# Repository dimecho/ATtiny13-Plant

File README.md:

# ATtiny13 Plant

Monitor soil moisture and water plant. Portable and high efficiency with lithium-ion batteries.

## Download

 [MacOS](../../releases/download/1.0/ATtiny13-Plant.dmg)

 [Windows](../../releases/download/1.0/ATtiny13-Plant.zip)

 [Linux](../../releases/download/1.0/ATtiny13-Plant.tgz)

 [Firmware](../../releases/download/1.0/ATtiny13-Plant-Firmware.zip)

## BOM (Bill of Materials)

| Part  | Value      | Package             | Function |
| ----- |:----------:| -------------------:|---------:|
| IC1   | ATTINY13A  | SOP-8 or DIP-8      | CPU      |
| C1    | 100nF      | 0805 or 0603 (104)  | CPU      |
| T1A/B | 2N4401 NPN | TO-92 or SOT-23     | Pump     |
| R1    | 100R       | 0805 or 0603 (101)  | Pump     |
| R2    | 10k        | 0805 or 0603 (103)  | Pump     |
| R6    | 10k        | 0805 or 0603 (103)  | Sensor   |
| LED1  | Red        | 0805 or DIP-2       | LED      |
| R7    | 1k         | 0805 or 0603 (102)  | LED      |
| -     | 3.7-4.2V   | Lithium 18650       | Battery  |
| -     | TP4056     | Lithium Charger     | Charger  |

## PCB

Designed with [EagleCAD](https://www.autodesk.com/products/eagle/free-download)

## Diagram

## Compile

Install "avr-gcc" and run "make".

> [MacOS](https://ww1.microchip.com/downloads/en/DeviceDoc/avr8-gnu-toolchain-osx-3.6.2.503-darwin.any.x86_64.tar.gz)
>
> [Windows](https://ww1.microchip.com/downloads/en/DeviceDoc/avr8-gnu-toolchain-3.6.2.1759-win32.any.x86.zip)

```
avr-gcc -std=gnu99 -Wall -Os -mmcu=attiny13a main.c -o main.o
avr-objcopy -O binary main.o main.bin
avr-objcopy -O ihex main.o main.hex
```

## Flash

```
avrdude -p t13 -c usbtiny -Uhfuse:w:0xFB:m -Ulfuse:w:0x6A:m -U flash:w:main.hex:i
```

There are 3 options to flash ATtiny13 chip.

1. [USBtiny](usbtiny) (built-in)
2. [USBasp](usbasp)
3. [Raspberry Pi](usbpi)

## Licenses

> ATtiny13 Plant
>
> 
>
> USBasp / USBtiny
>
>

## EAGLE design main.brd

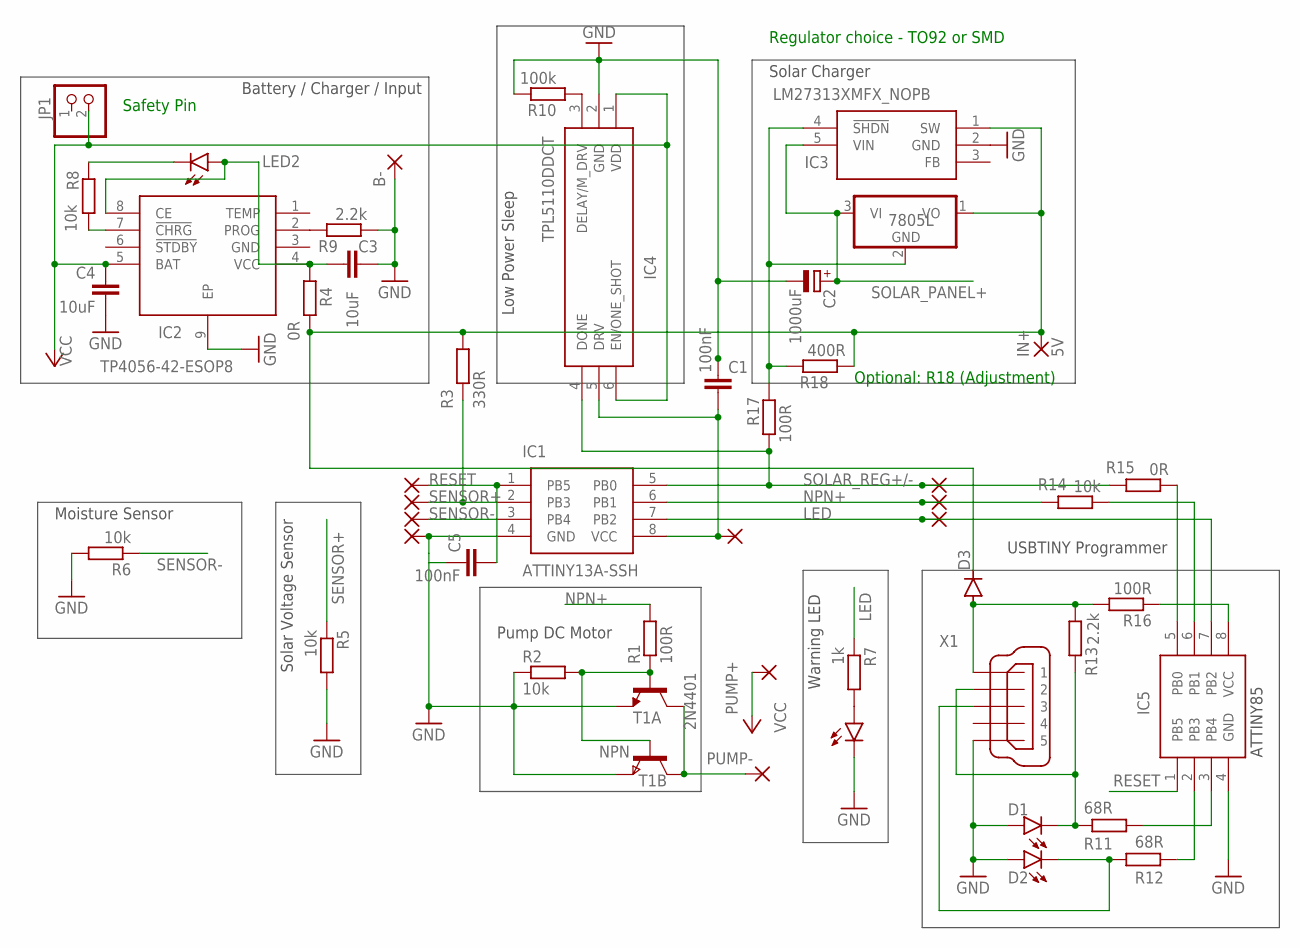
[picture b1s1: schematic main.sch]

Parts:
B-: 1,6/0,8
C1, C5: 100nF; C0805
C2: 1000uF; E2,5-7
C3: 10uF; C3216
C4: 10uF; C0805
D1, D2: LEDSML0805; SML0805
D3: DIODE-MINIMELF; MINIMELF
IC1, IC5: ATTINY13A-SSH; SOIC127P600X175-8N
IC2: TP4056-42-ESOP8; SOIC127P600X175-9N
IC3: LM27313XMFX_NOPB; SOT95P280X145-5N
IC4: TPL5110DDCT; SOT95P280X110-6N
IN+: 5V; 1,6/0,9
JP1: PINHD-1X2; 1X02
LED1, LED2: LEDSML0805; SML0805
PAD3, PAD4, PAD5, PAD6, PAD7, PAD8, PAD9, PAD10: 1,6/0,8
PUMP+: 2,15/1,0
PUMP-: 2,15/1,0
R1: 100R; R0805
R2, R5, R6: 10k; R0805
R3: 330R; R0805
R4: 0R; M1206
R7: 1k; R0805
R8: 10k; R0603
R9, R13: 2.2k; R0603
R10: 100k; R0603
R11, R12: 68R; R0603
R14: 10k; R0402
R15: 0R; R0402
R16, R17: 100R; R0603
R18: 400R; R0603
REG1: 7805L; TO92
T1A: 2N4401; TO92
T1B: NPN; SOT-23
X1: MINI-USB-UX60A-MB-5ST; UX60A-MB-5ST

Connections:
GND: B-.1, C1.1, C2.-, C3.2, C4.2, C5.1, D1.A, D2.A, IC1.4 (GND), IC2.9 (EP), IC3.2 (GND), IC4.2 (GND), IC5.4 (GND), LED1.C, PAD7.1, R2.1, R5.2, R6.2, R9.2, R10.2, T1A.1 (E), T1B.2 (E), X1.5
LED: IC1.7 (PB2), IC5.7 (PB2), PAD4.1, R7.1
unnamed: R1.1, R2.2, T1A.2 (B), T1B.3 (B)
unnamed: PUMP-.1, T1A.3 (C), T1B.1 (C)
unnamed: C1.2, IC1.8 (VCC), IC4.5 (DRV), PAD3.1
unnamed: C3.1, IC2.4 (VCC), IC2.8 (CE), LED2.A, R4.2
unnamed: D3.C, IC3.1 (SW), IN+.1, R3.2, R4.1, R18.1, REG1.1 (VO)
unnamed: LED1.A, R7.2
unnamed: IC4.3 (DELAY/M_DRV), R10.1
unnamed: IC2.7 (!CHRG), R8.2
unnamed: LED2.C, R8.1
unnamed: IC5.3 (PB4), R11.2
unnamed: IC2.2 (PROG), R9.1
unnamed: IC5.2 (PB3), R12.2
unnamed: D1.C, R11.1, R13.2, X1.2
unnamed: D2.C, R12.1, X1.3
unnamed: IC5.6 (PB1), R14.1
unnamed: IC5.5 (PB0), R15.1
unnamed: IC5.8 (VCC), R16.1
unnamed: IC3.4 (!SHDN), R17.2, R18.2, REG1.2 (GND)
unnamed: D3.A, R13.1, R16.2, X1.1
NPN+: IC1.6 (PB1), PAD6.1, R1.2, R14.2
RESET: C5.2, IC1.1 (PB5), IC5.1 (PB5), PAD10.1
SENSOR+: IC1.2 (PB3), PAD9.1, R3.1, R5.1
SENSOR-: IC1.3 (PB4), PAD8.1, R6.1
SOLAR_PANEL+: C2.+, IC3.5 (VIN), REG1.3 (VI)
SOLAR_REG+/-: IC1.5 (PB0), IC4.4 (DONE), PAD5.1, R15.2, R17.1
VCC: C4.1, IC2.5 (BAT), IC4.1 (VDD), IC4.6 (EN/ONE_SHOT), JP1.2, PUMP+.1

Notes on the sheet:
Battery / Charger / Input
Solar Charger
Pump DC Motor
Warning LED
Moisture Sensor
Solar Voltage Sensor
Low Power Sleep
ATTINY85
USBTINY Programmer
Safety Pin
Regulator choice - TO92 or SMD
Optional: R18 (Adjustment)

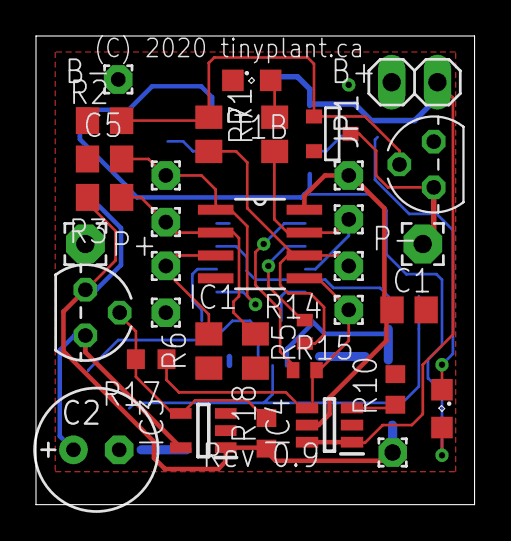
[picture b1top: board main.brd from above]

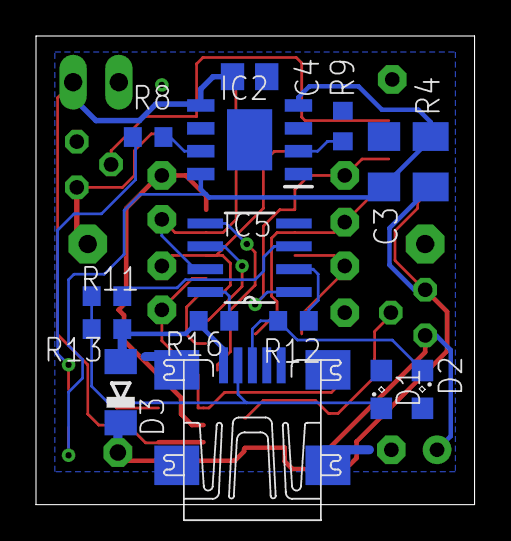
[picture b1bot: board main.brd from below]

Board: 2 copper layers, 24.4 x 26.0 mm, 50 parts (15 on the bottom side), 28 nets.

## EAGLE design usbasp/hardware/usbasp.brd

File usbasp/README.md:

USBASP KEY
==========

http://fabiobaltieri.com/2011/09/02/usb-key-avr-programmer/

This project is an AVR ISP programmer with USB interface in a compact usb
key PCB. The project is based on the original USBasp version of Thomas Fischl,
which can be found on:

http://www.fischl.de/usbasp/

Contents
--------

    COPYING     text version of the GPL
    README      this file
    binaries/   pre-built firmware images in hex format
    firmware/   source directory for firmware files
    hardware/   source directory for the hardware design files

Firmware
--------

Building requires an avr-gcc toolchain, in the firmware/ directory, to build
run:

    make main.hex

Flashing the firmware on the device requires avrdude and a compatible hardware
programmer. Default configuration is stored at the beginning of the Makefile.
To program with the default configuration, run:

    make flash

Fuses can be configured running:

    make fuses

Hardware
--------

All hardware files (schematic, layout and libraries) are in CadSoft Eagle
format.

```
avrdude -p t13 -c usbasp -Uhfuse:w:0xFB:m -Ulfuse:w:0x6A:m -U flash:w:main.hex:i
```

License
-------

This program is free software: you can redistribute it and/or modify
it under the terms of the GNU General Public License as published by
the Free Software Foundation, either version 2 of the License, or
(at your option) any later version.

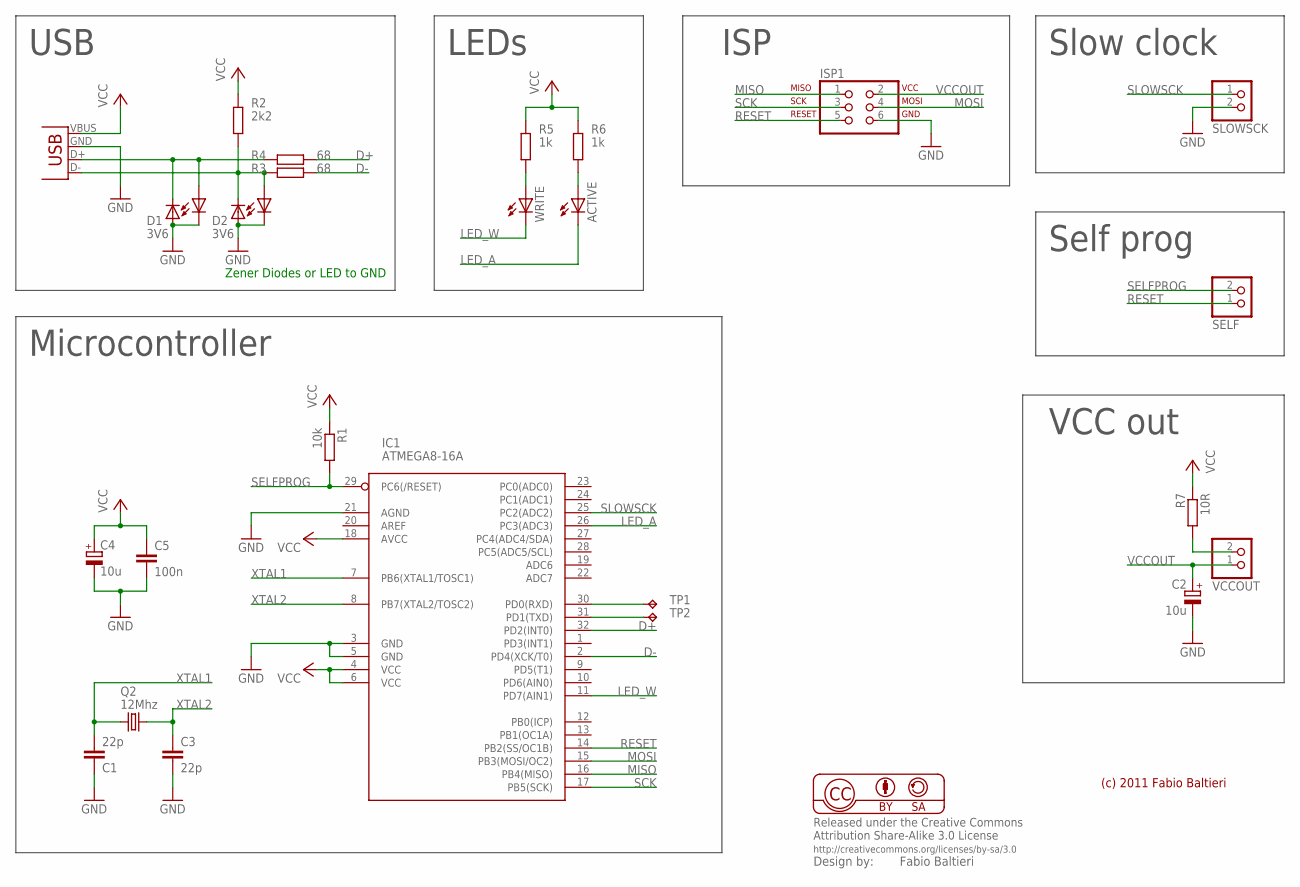
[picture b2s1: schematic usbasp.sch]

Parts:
ACTIVE: LEDCHIP-LED0805; CHIP-LED0805
C1, C3: 22p; C0805
C2, C4: 10u; SMC_A
C5: 100n; C0805
D1, D2: 3V6; SMA-DIODE
IC1: ATMEGA8-16A; TQFP32-08
ISP1: ISP-AVR910SMD; 2X03_BORDER
LED1, LED2: LEDCHIP-LED0805; CHIP-LED0805
Q2: 12Mhz; HC49US
R1: 10k; M0805
R2: 2k2; M0805
R3, R4: 68; M0805
R5, R6: 1k; M0805
R7: 10R; M0805
SELF: PINHD-1X2; 1X02
SLOWSCK: PINHD-1X2; 1X02
TP1, TP2: TPB1,27; B1,27
VCCOUT: PINHD-1X2; 1X02
WRITE: LEDCHIP-LED0805; CHIP-LED0805
X1: USB-A-H

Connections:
D+: IC1.32 (PD2(INT0)), R4.1
D-: IC1.2 (PD4(XCK/T0)), R3.1
GND: C1.1, C2.-, C3.1, C4.-, C5.2, D1.A, D2.A, IC1.3 (GND), IC1.5 (GND), IC1.21 (AGND), ISP1.6, LED1.C, LED2.C, SLOWSCK.2, X1.GND (VBUS)
LED_A: ACTIVE.C, IC1.26 (PC3(ADC3))
LED_W: IC1.11 (PD7(AIN1)), WRITE.C
MISO: IC1.16 (PB4(MISO)), ISP1.1
MOSI: IC1.15 (PB3(MOSI/OC2)), ISP1.4
unnamed: R5.2, WRITE.A
unnamed: D1.C, LED1.A, R4.2, X1.D+ (D-)
unnamed: D2.C, LED2.A, R2.1, R3.2, X1.D- (D+)
unnamed: ACTIVE.A, R6.2
unnamed: IC1.30 (PD0(RXD)), TP1.TP
unnamed: R7.2, VCCOUT.2
unnamed: IC1.31 (PD1(TXD)), TP2.TP
RESET: IC1.14 (PB2(SS/OC1B)), ISP1.5, SELF.1
SCK: IC1.17 (PB5(SCK)), ISP1.3
SELFPROG: IC1.29 (PC6(/RESET)), R1.2, SELF.2
SLOWSCK: IC1.25 (PC2(ADC2)), SLOWSCK.1
VCC: C4.+, C5.1, IC1.4 (VCC), IC1.6 (VCC), IC1.18 (AVCC), R1.1, R2.2, R5.1, R6.1, R7.1, X1.VBUS (GND)
VCCOUT: C2.+, ISP1.2, VCCOUT.1
XTAL1: C1.2, IC1.7 (PB6(XTAL1/TOSC1)), Q2.2
XTAL2: C3.2, IC1.8 (PB7(XTAL2/TOSC2)), Q2.1

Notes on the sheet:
(c) 2011 Fabio Baltieri
Microcontroller
USB
LEDs
ISP
Slow clock
Self prog
VCC out
Zener Diodes or LED to GND

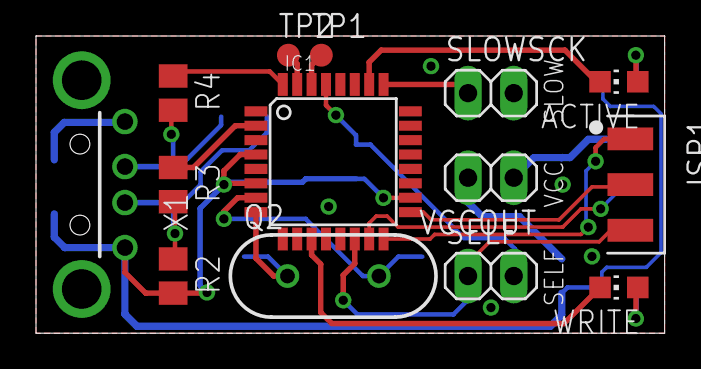
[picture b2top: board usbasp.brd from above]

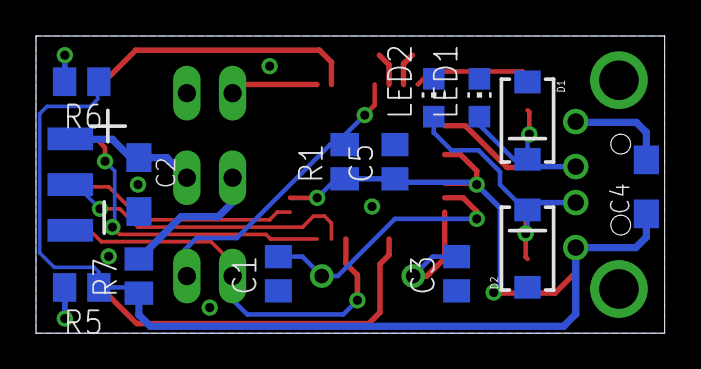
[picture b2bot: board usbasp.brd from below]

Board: 2 copper layers, 34.9 x 16.5 mm, 27 parts (13 on the bottom side), 22 nets.

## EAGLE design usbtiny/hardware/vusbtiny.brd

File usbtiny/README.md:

http://www.simpleavr.com/avr/vusbtiny

Description
-------

From http://www.xs4all.nl/~dicks/avr/usbtiny/

USBtiny is a software implementation of the USB low-speed protocol for the Atmel ATtiny microcontrollers. Of course, it will also work on the ATmega series. The software is written for an AVR clocked at 12 MHz. At this frequency, each bit on the USB bus takes 8 clock cycles, and with a lot of trickery, it is possible to decode and encode the USB waveforms by software. The USB driver needs approximately 1250 to 1350 bytes of flash space (excluding the optional identification strings), depending on the configuration and compiler version, and 46 bytes RAM (excluding stack space). The C interface consists of 3 to 5 functions, depending on the configuration.

vUSB
-------

From http://www.obdev.at/products/vusb/

V-USB is a software-only implementation of a low-speed USB device for Atmel's AVR microcontrollers, making it possible to build USB hardware with almost any AVR microcontroller, not requiring any additional chip.

Features
-------

* Programming logic from usbtiny isp, mature avr-dude support
* Small foot-print
* Minimal components
* Powers target device

Note that the IO lines to the target MCUS are not protected. you can add 1k-2k resistors to SCK and MOSI and protect against possible wrong connections

References
-------

based on the works found at

v-usb from framework http://www.obdev.at/vusb/
usbtiny isp http://www.xs4all.nl/~dicks/avr/usbtiny/

Parts List
-------

* 1x attiny45/85
* 1x 100nf capacitor (104)
* 2x 3.6v zener diodes (1n747,BZX79)
* 2x 68ohm resistor
* 1x 1.5k (1.7k) resistor

* (optional) 1k/2k resistors for io lines protection

Tools Required
-------
* A working AVR programmer (yes, it's a catch22, we need one to make one)
* Working AVR programming environment

Application Notes
-------

* vusbtiny works with avrdude and is viewed by avrdude as a usbtiny programmer
* vusbtiny always power target chip via USB
* Jumper J2 connects programmer to target chip
* When connected and NOT in programming
* Target chip w/ target RESET line high
* Other target pins (MISO, MOSI, CLK) in hi-Z state
* During programming
* Turns target RESET line LOW
* MISO becomes input
* MOSI, CLK becomes output

Schematic
-------

Building and Flashing
-------

* change into /firmware working directory
```
make
```
* attach your favorite ISP programmer
* modify makefile and change your avrdude parameters if needed. the stock one assumes USBTiny programmer. i.e. AVRDUDE_PROGRAMMERID=usbtiny
```
make install
```
After flashing firmware, we need to properly set the fuse, we are using pin 1 reset as IO in this project

* PLL clock used as required by v-usb layer for usb timing (16.5Mhz)
* reset pin disabled as we need to use it as IO
```
avrdude -c usbtiny -p t85 -V -U lfuse:w:0xe1:m -U hfuse:w:0x5d:m -U efuse:w:0xff:m
```

This setting disables further programming via 5V SPI as we need the RESET pin (pin1) for IO. you will need access to a HVSP programmer to recover the fuse.

Troubleshooting
-------

* Cannot flash the firmware? check your original programmer, might need to adjust timing via -B flag in avrdude. try to read chip 1st, may be a bad fuse, may be your chip need an external clock signal. you may need to fix your chip back to default 1st.
    check connections
* If use different io pins, check code and connections
* You may substitute zener diodes with 500mw, 400mw types
* You may try reduce R3 value to 1.2K or less
* You are more likely to encounter avrdude timing problems, try -B flag of avrdude, have a shorter USB cable all helps

License
-------

GPL2

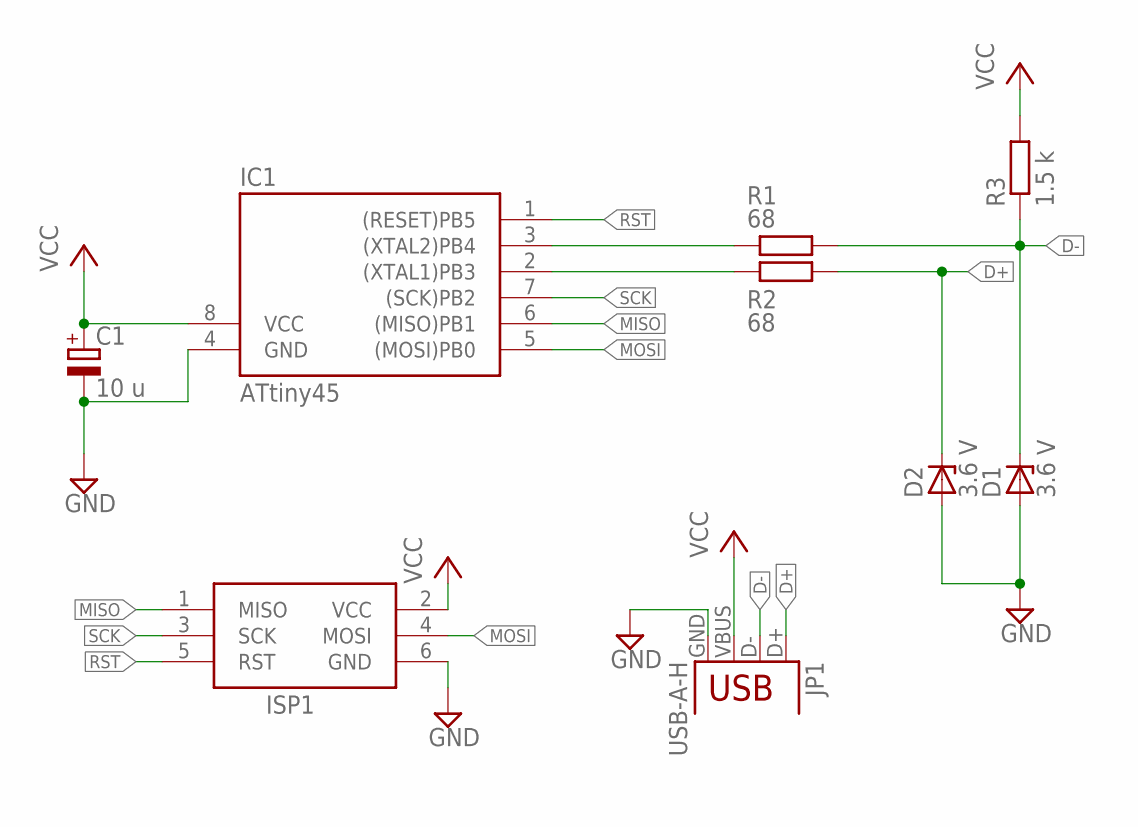
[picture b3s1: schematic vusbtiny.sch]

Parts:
C1: 10 u; E2,5-5
D1, D2: 3.6 V; DO34Z7
IC1: ATtiny45; DIL08
ISP1: AVRISP-6; AVRISP
JP1: USB-A-H
R1, R2: 68; 0207/10
R3: 1.5 k; 0207/10

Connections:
D+: D2.C, JP1.D+, R2.2
D-: D1.C, JP1.D-, R1.2, R3.1
GND: C1.-, D1.A, D2.A, IC1.4 (GND), ISP1.6 (GND), JP1.GND
MISO: IC1.6 ((MISO)PB1), ISP1.1 (MISO)
MOSI: IC1.5 ((MOSI)PB0), ISP1.4 (MOSI)
unnamed: IC1.3 ((XTAL2)PB4), R1.1
unnamed: IC1.2 ((XTAL1)PB3), R2.1
RST: IC1.1 ((RESET)PB5), ISP1.5 (RST)
SCK: IC1.7 ((SCK)PB2), ISP1.3 (SCK)
VCC: C1.+, IC1.8 (VCC), ISP1.2 (VCC), JP1.VBUS, R3.2

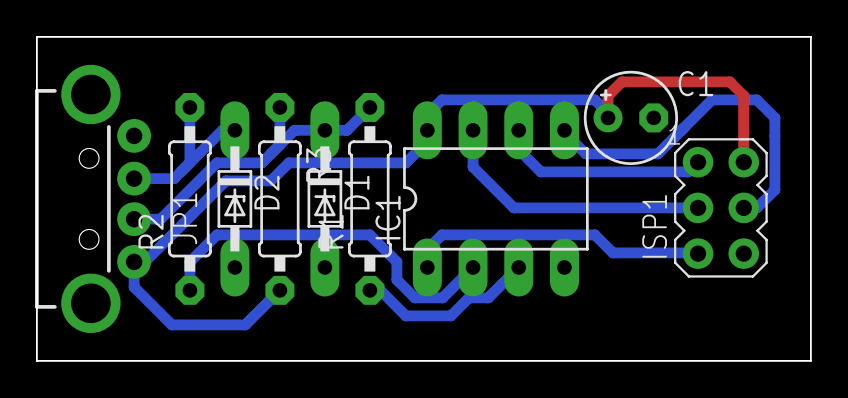
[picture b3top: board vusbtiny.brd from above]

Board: 2 copper layers, 43.0 x 18.0 mm, 9 parts (0 on the bottom side), 10 nets.

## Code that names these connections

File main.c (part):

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/*
                             [ATtiny13A]
                              +------+
                [RESET] PB5  1| O    |8  VCC (2.7V - 4.8V)
(Sensor OUT / Solar IN) PB3  2|      |7  PB2 [CLK]  (LED)
(Sensor IN)             PB4  3|      |6  PB1 [MISO] (Pump)
                        GND  4|      |5  PB0 [MOSI] (Solar ON (WS78L05) / Sleep (TPL5110))
                              +------+
*/
#ifndef SERIAL
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 #define potSizeTimer               20 //20x2x100 = 4000 miliseconds (minus 1 seconds prime) = 3 seconds pump
#endif

#define pumpPin                     PB1 //Output
#define sensorPin                   PB3 //Output
#define solarPin                    PB0 //Output
#define ledPin                      PB2 //Output
#define solarSensorPin              PB3 //Input/Output
#define moistureSensorPin           PB4 //Input
#define delayWatering               50  //8 seconds x 50 = 6.5 min
#define delayBetweenRefillReset     20  //8 seconds x 40 x 20 = 2 hours
#define delayBetweenOverfloodReset  100 //8 seconds x 40 x 100 = 8 hours
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
#ifdef UART_TX_ENABLED
    #define TXDELAY         (uint8_t)(((F_CPU/UART_BAUDRATE)-7 +1.5)/3)
    #define UART_TX         PB3 // Use PB3 as TX pin
    void uart_putc(char c);
    void uart_putu(uint16_t x);
    void uart_puts(const char *s);
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#ifdef UART_RX_ENABLED
    #define RXDELAY          (int)(((F_CPU/UART_BAUDRATE)-5 +1.5)/3)
    #define RXDELAY2         (int)((RXDELAY*1.5)-2.5)
    #define UART_RX          PB4 // Use PB4 as RX pin
    /*
    #define RXROUNDED         (((F_CPU/UART_BAUDRATE)-5 +2)/3)
    #if RXROUNDED > 127
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    //Page 57 ATtiny13 Manual
    //MCUCR = 0x40;	//All Pins Pull-up disabled
    DDRB = 0xFF;	//All Pins (0-0-DDB5-DDB4-DDB3-DDB2-DDB1-DDB0)	OUTPUT = 1 | INPUT = 0
    PORTB = 0x00;   //All Pins (0-0-PB5-PB4-PB3-PB2-PB1-PB0)        ON = 1 | OFF = 0
    blink(10,4);	//Alive blink

    //=============
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        //================
        //BODCR |= (1<<BODS)|(1<<BODSE); //Disable Brown Out Detector Control Register
        /*
        PORTB |= (1<<PB0); //ON
        _delay_ms(900);
        PORTB &= ~(1<<PB0); //OFF
        */
        uart_putc('.');
        uart_putu(versionID);
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                    //Detect Empty Bottle (Sensored)
                    //===================
                    /*
                    loopback wire from water jug to Pin3 (PB4)
                    given power from Pin5 (PB0) while turning on NPN transistor
                    more accurate than sensor-less detection
                    */
                    /*
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                //======================
                // Low Voltage Warning
                //======================
                voltage = ReadADC(PB5, 5); //Self-VCC @ 5Vref
                //DEBUG
                /*for (uint8_t i = 100 ; i >= 1; i /= 10) {
                    uint8_t d = (voltage/i) % 10;
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    #endif

    /*
    if(pin == PB5) { // ADC0
        ADMUX |= (0 << MUX0) | (0 << MUX1); //ADC0 PB5 as analog input channel
    }else if(pin == PB2) { // ADC1
        ADMUX |= (1 << MUX0) | (0 << MUX1); //ADC1 PB2 as analog input channel
    }*/

    if(pin == PB3) { // ADC3
        ADMUX = (1 << MUX0) | (1 << MUX1); //ADC3 PB3 as analog input channel
    }else if (pin == PB4){ // ADC2
        ADMUX = (0 << MUX0) | (1 << MUX1); //ADC2 PB4 as analog input channel
    }

    //--------------
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
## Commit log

2018-05-20 schematics update
2018-06-11 fixed empty detection
2018-06-11 readme
2018-06-13 code corrections
2018-11-17 prevent dry lock-ups
2019-01-13 added pcb design
2019-01-14 pcb adjustments
2019-01-14 a few more corrections
2019-01-15 optimized pcb and code
2019-01-16 Rev 0.3
2019-01-18 Rev 0.4
2019-02-09 Rev 0.5
2019-03-04 added eeprom read/write
2019-03-04 optimized code
2019-03-05 added version track
2019-06-29 added flood protection
2019-06-30 a few optimizations
2019-07-01 code update version 1.3
2019-07-07 added experimental bootloader
2019-07-09 code updates
2019-07-13 rev 0.6
2019-07-14 added switching regulator
2019-07-15 calibrated solar
2019-07-17 solar parameters tuned
2019-08-15 calibrated battery
2019-08-18 added gui interface
2019-12-24 new graphics
2019-12-26 gui updates
2019-12-27 removed bootloader added USBasp
2019-12-29 windows drivers
2020-01-01 improved solar
2020-01-03 remapped LED gpio
2020-02-05 many updates
2020-02-12 added usbtiny + many updates
2020-02-15 rev 0.8 (usbtiny built-in)
2020-02-22 better cert signing
2020-03-24 improved clock calibration
2020-03-28 lots of updates
2020-03-29 rev 0.9
2020-04-02 changed ADC ref to 1.1V
2020-04-05 added operational diagram
2020-04-07 fixed linux and added graph
2020-04-13 added usb diode
2020-04-13 low battery detection
2020-04-16 adc noise reduction code
2020-04-21 code refactoring
2020-04-22 reset pin filter capacitor
2020-04-23 code reorganized
2020-04-24 major bug fix - force pump turn off
2020-05-03 firmware updates
2020-05-05 better settings retry loop
2020-05-09 another bug fix
2020-05-29 added manual timer feature
2020-06-01 timer code fix
2020-06-06 eeprom uint16 value fix

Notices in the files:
README.md:
Licenses:
> [CC BY-SA 4.0](https://creativecommons.org/licenses/by-sa/4.0/legalcode)
> USBasp / USBtiny
> [GNU](https://www.gnu.org/licenses/)
main.brd:
(C) 2020 tinyplant.ca
parts and their libraries:
balto: Released under the Creative Commons
balto: http://creativecommons.org/licenses/by-sa/3.0
SparkFun-Connectors: Licensing: Creative Commons ShareAlike 4.0 International - https://creativecommons.org/licenses/by-sa/4.0
